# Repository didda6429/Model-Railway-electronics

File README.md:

# Model-Railway-electronics
The electronics hardware for the servo-motors controlling the switches on my model railway. As I finalise the software and other components, they will be added here. 

For more information, see my blog at www.cablepi.com

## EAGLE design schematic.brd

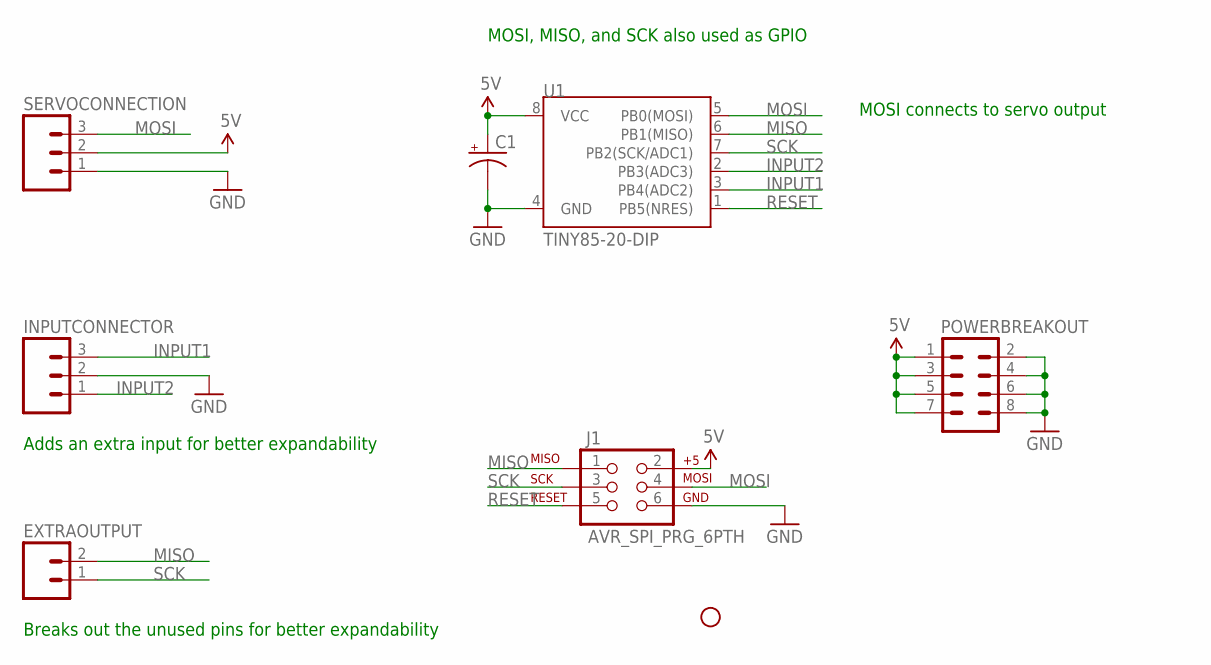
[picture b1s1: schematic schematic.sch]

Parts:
C1: 10UF-25V-20%(PTH); CPOL-RADIAL-10UF-25V
EXTRAOUTPUT: M02PTH; 1X02
H1: STAND-OFF
INPUTCONNECTOR: M03PTH; 1X03
J1: AVR_SPI_PRG_6PTH; 2X3
POWERBREAKOUT: M04X2; 2X4
SERVOCONNECTION: M03PTH; 1X03
U1: TINY85-20-DIP; DIP08

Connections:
5V: C1.1 (+), J1.2, POWERBREAKOUT.1, POWERBREAKOUT.3, POWERBREAKOUT.5, POWERBREAKOUT.7, SERVOCONNECTION.2, U1.8 (VCC)
GND: C1.2 (-), INPUTCONNECTOR.2, J1.6, POWERBREAKOUT.2, POWERBREAKOUT.4, POWERBREAKOUT.6, POWERBREAKOUT.8, SERVOCONNECTION.1, U1.4 (GND)
INPUT1: INPUTCONNECTOR.3, U1.3 (PB4(ADC2))
INPUT2: INPUTCONNECTOR.1, U1.2 (PB3(ADC3))
MISO: EXTRAOUTPUT.2, J1.1, U1.6 (PB1(MISO))
MOSI: J1.4, SERVOCONNECTION.3, U1.5 (PB0(MOSI))
RESET: J1.5, U1.1 (PB5(NRES))
SCK: EXTRAOUTPUT.1, J1.3, U1.7 (PB2(SCK/ADC1))

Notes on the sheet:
MOSI, MISO, and SCK also used as GPIO
MOSI connects to servo output
Adds an extra input for better expandability
Breaks out the unused pins for better expandability

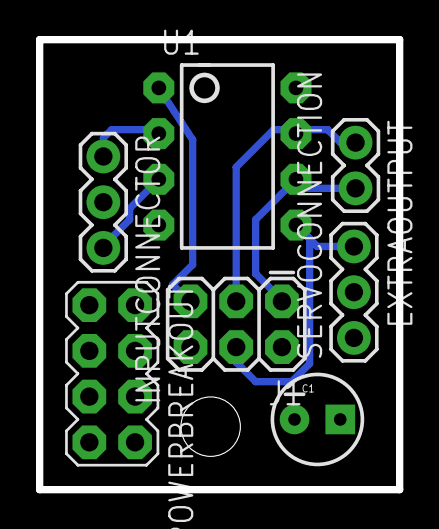
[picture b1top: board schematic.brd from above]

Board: 2 copper layers, 20.0 x 25.0 mm, 8 parts (0 on the bottom side), 8 nets.

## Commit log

2016-11-10 Adds schematic and board layout files
2016-11-10 Create license
    Adds the GNU GPLv3 license
2017-05-10 Adds the software for the attiny85 nodes
2017-05-10 Rename ServoSoftware.ino.ino to ServoSoftware.ino
2017-05-10 fixes folder structure

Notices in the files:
parts and their libraries:
SparkFun-Capacitors: Licensing: Creative Commons ShareAlike 4.0 International - https://creativecommons.org/licenses/by-sa/4.0
